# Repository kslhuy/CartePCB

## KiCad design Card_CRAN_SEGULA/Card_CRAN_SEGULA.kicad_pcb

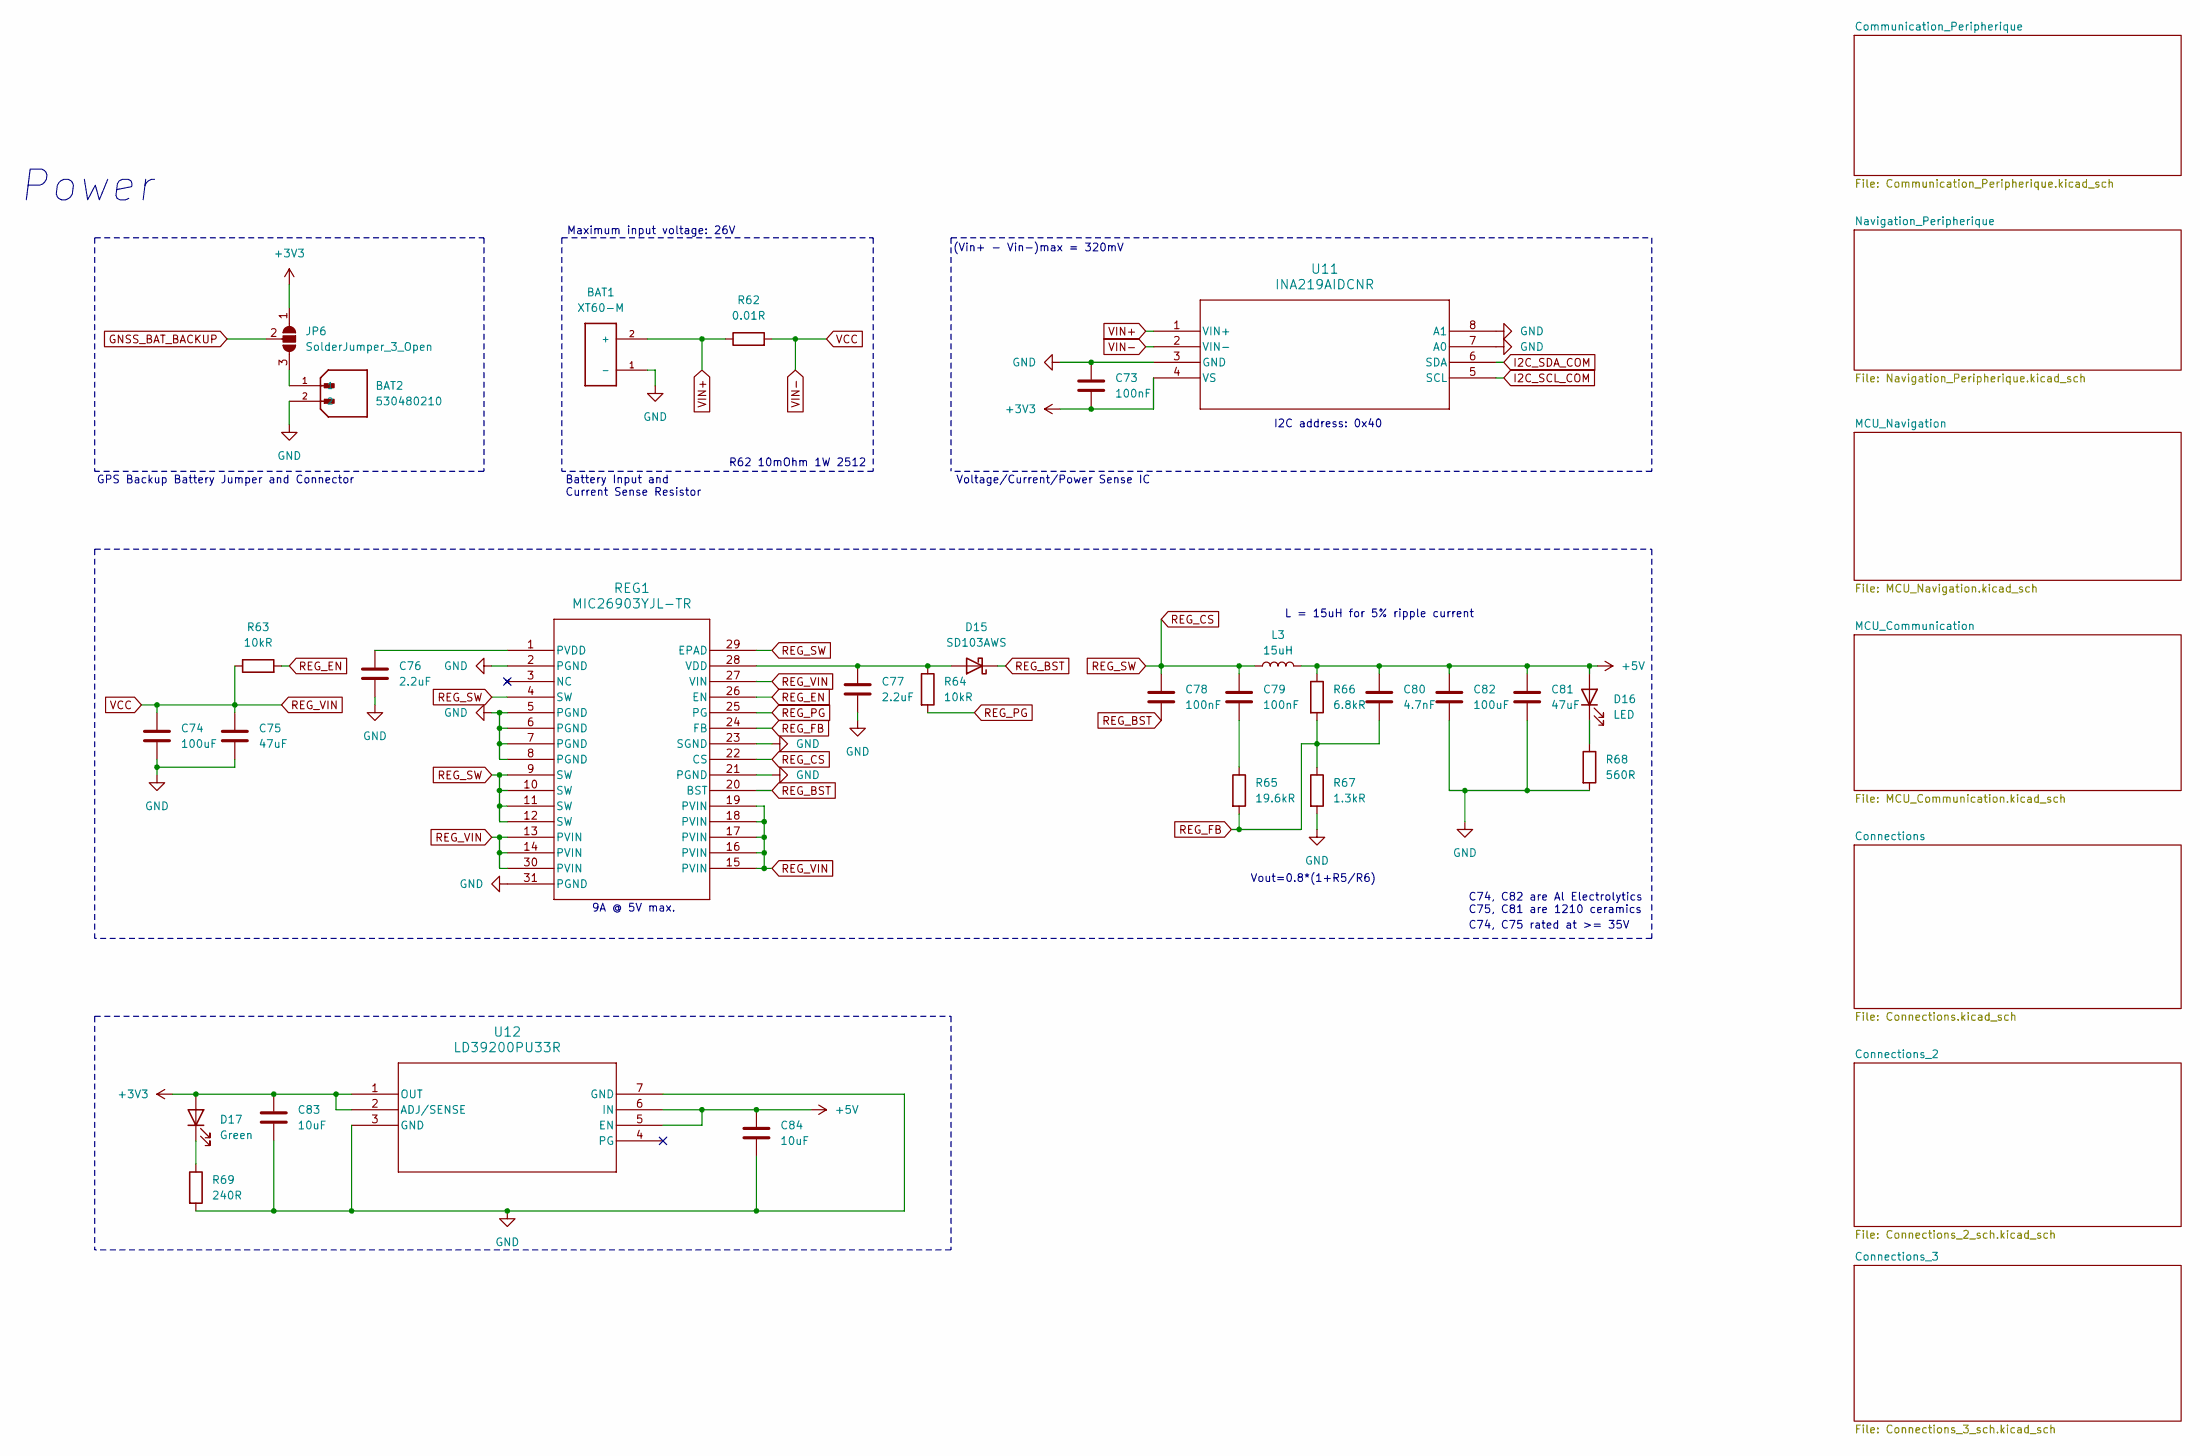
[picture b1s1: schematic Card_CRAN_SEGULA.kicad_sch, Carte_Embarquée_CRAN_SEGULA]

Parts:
BAT1: XT60-M; AMASS_XT60-M
BAT2: 530480210; MOLEX_530480210; PARTREV A
C73: 100nF; CAPC1005X55N
C74, C82: 100uF; CAP_EEEFPV101XAV
C75, C81: 47uF; CAP_C5750X7R1V476M230KC
C76, C77: 2.2uF; CAPC220145_140N_KEM
C78, C79: 100nF; CAPC230155_120N_KEM
C80: 4.7nF; CAPC220145_100N_KEM
C83, C84: 10uF; CAPC1608X100N
D15: SD103AWS; D_SOD-323
D16: LED; 599-0081-007F_DIA
D17: Green; 599-0081-007F_DIA
JP6: SolderJumper_3_Open; SolderJumper-3_P1.3mm_Open_RoundedPad1.0x1.5mm
L3: 15uH; IND_SRP1265A-150M
R62: 0.01R; RES_PE2512_YAG
R63, R64: 10kR; RESC2012X70N
R65: 19.6kR; RES_ERJ-PB6B1962V
R66: 6.8kR; RESC2012X60N
R67: 1.3kR; RK73H2ATTD1301F
R68: 560R; RES_ERJPA3F5600V
R69: 240R; RES_ERJPA3F2400V
REG1: MIC26903YJL-TR; MIC24054YJLTR
U11: INA219AIDCNR; DCN8
U12: LD39200PU33R; SON_DFN6_3X3_STM

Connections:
+5V: C80.1, C81.1, C82.1, C84.1, D16.2 (A), L3.2, R66.1, U12.5 (EN), U12.6 (IN); also elsewhere on the board
GND: BAT1.1 (-), BAT2.2, C73.1, C74.2, C75.2, C76.2, C77.2, C81.2, C82.2, C83.2, C84.2, R67.2, R68.2, R69.2, REG1.2 (PGND), REG1.5 (PGND), REG1.6 (PGND), REG1.7 (PGND), REG1.8 (PGND), REG1.21 (PGND), REG1.23 (SGND), REG1.31 (PGND), U11.3 (GND), U11.7 (A0), U11.8 (A1), U12.3 (GND), U12.7 (GND); also elsewhere on the board
GNSS_BAT_BACKUP: JP6.2 (C); also elsewhere on the board
I2C_SCL_COM: U11.5 (SCL); also elsewhere on the board
I2C_SDA_COM: U11.6 (SDA); also elsewhere on the board
unnamed: C79.2, R65.1
unnamed: C77.1, D15.2 (A), R64.1, REG1.28 (VDD)
unnamed: D16.1 (K), R68.1
unnamed: D17.1 (K), R69.1
unnamed: BAT2.1, JP6.3 (B)
unnamed: C76.1, REG1.1 (PVDD)
REG_BST: C78.2, D15.1 (K), REG1.20 (BST)
REG_CS: C78.1, C79.1, L3.1, REG1.4 (SW), REG1.9 (SW), REG1.10 (SW), REG1.11 (SW), REG1.12 (SW), REG1.22 (CS), REG1.29 (EPAD)
REG_EN: R63.2, REG1.26 (EN)
REG_FB: C80.2, R65.2, R66.2, R67.1, REG1.24 (FB)
REG_PG: R64.2, REG1.25 (PG)
REG_VIN: C74.1, C75.1, R62.2, R63.1, REG1.13 (PVIN), REG1.14 (PVIN), REG1.15 (PVIN), REG1.16 (PVIN), REG1.17 (PVIN), REG1.18 (PVIN), REG1.19 (PVIN), REG1.27 (VIN), REG1.30 (PVIN), U11.2 (VIN-)
VIN+: BAT1.2 (+), R62.1, U11.1 (VIN+)
WIFI_BUCVBATS: C73.2, C83.1, D17.2 (A), JP6.1 (A), U11.4 (VS), U12.1 (OUT), U12.2 (ADJ/SENSE); also elsewhere on the board

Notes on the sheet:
Vout=0.8*(1+R5/R6)
R62 10mOhm 1W 2512
Maximum input voltage: 26V
9A @ 5V max.
Battery Input and Current Sense Resistor
I2C address: 0x40
C74, C82 are Al Electrolytics C75, C81 are 1210 ceramics
L = 15uH for 5% ripple current
Voltage/Current/Power Sense IC
GPS Backup Battery Jumper and Connector
(Vin+ - Vin-)max = 320mV
C74, C75 rated at >= 35V
Power

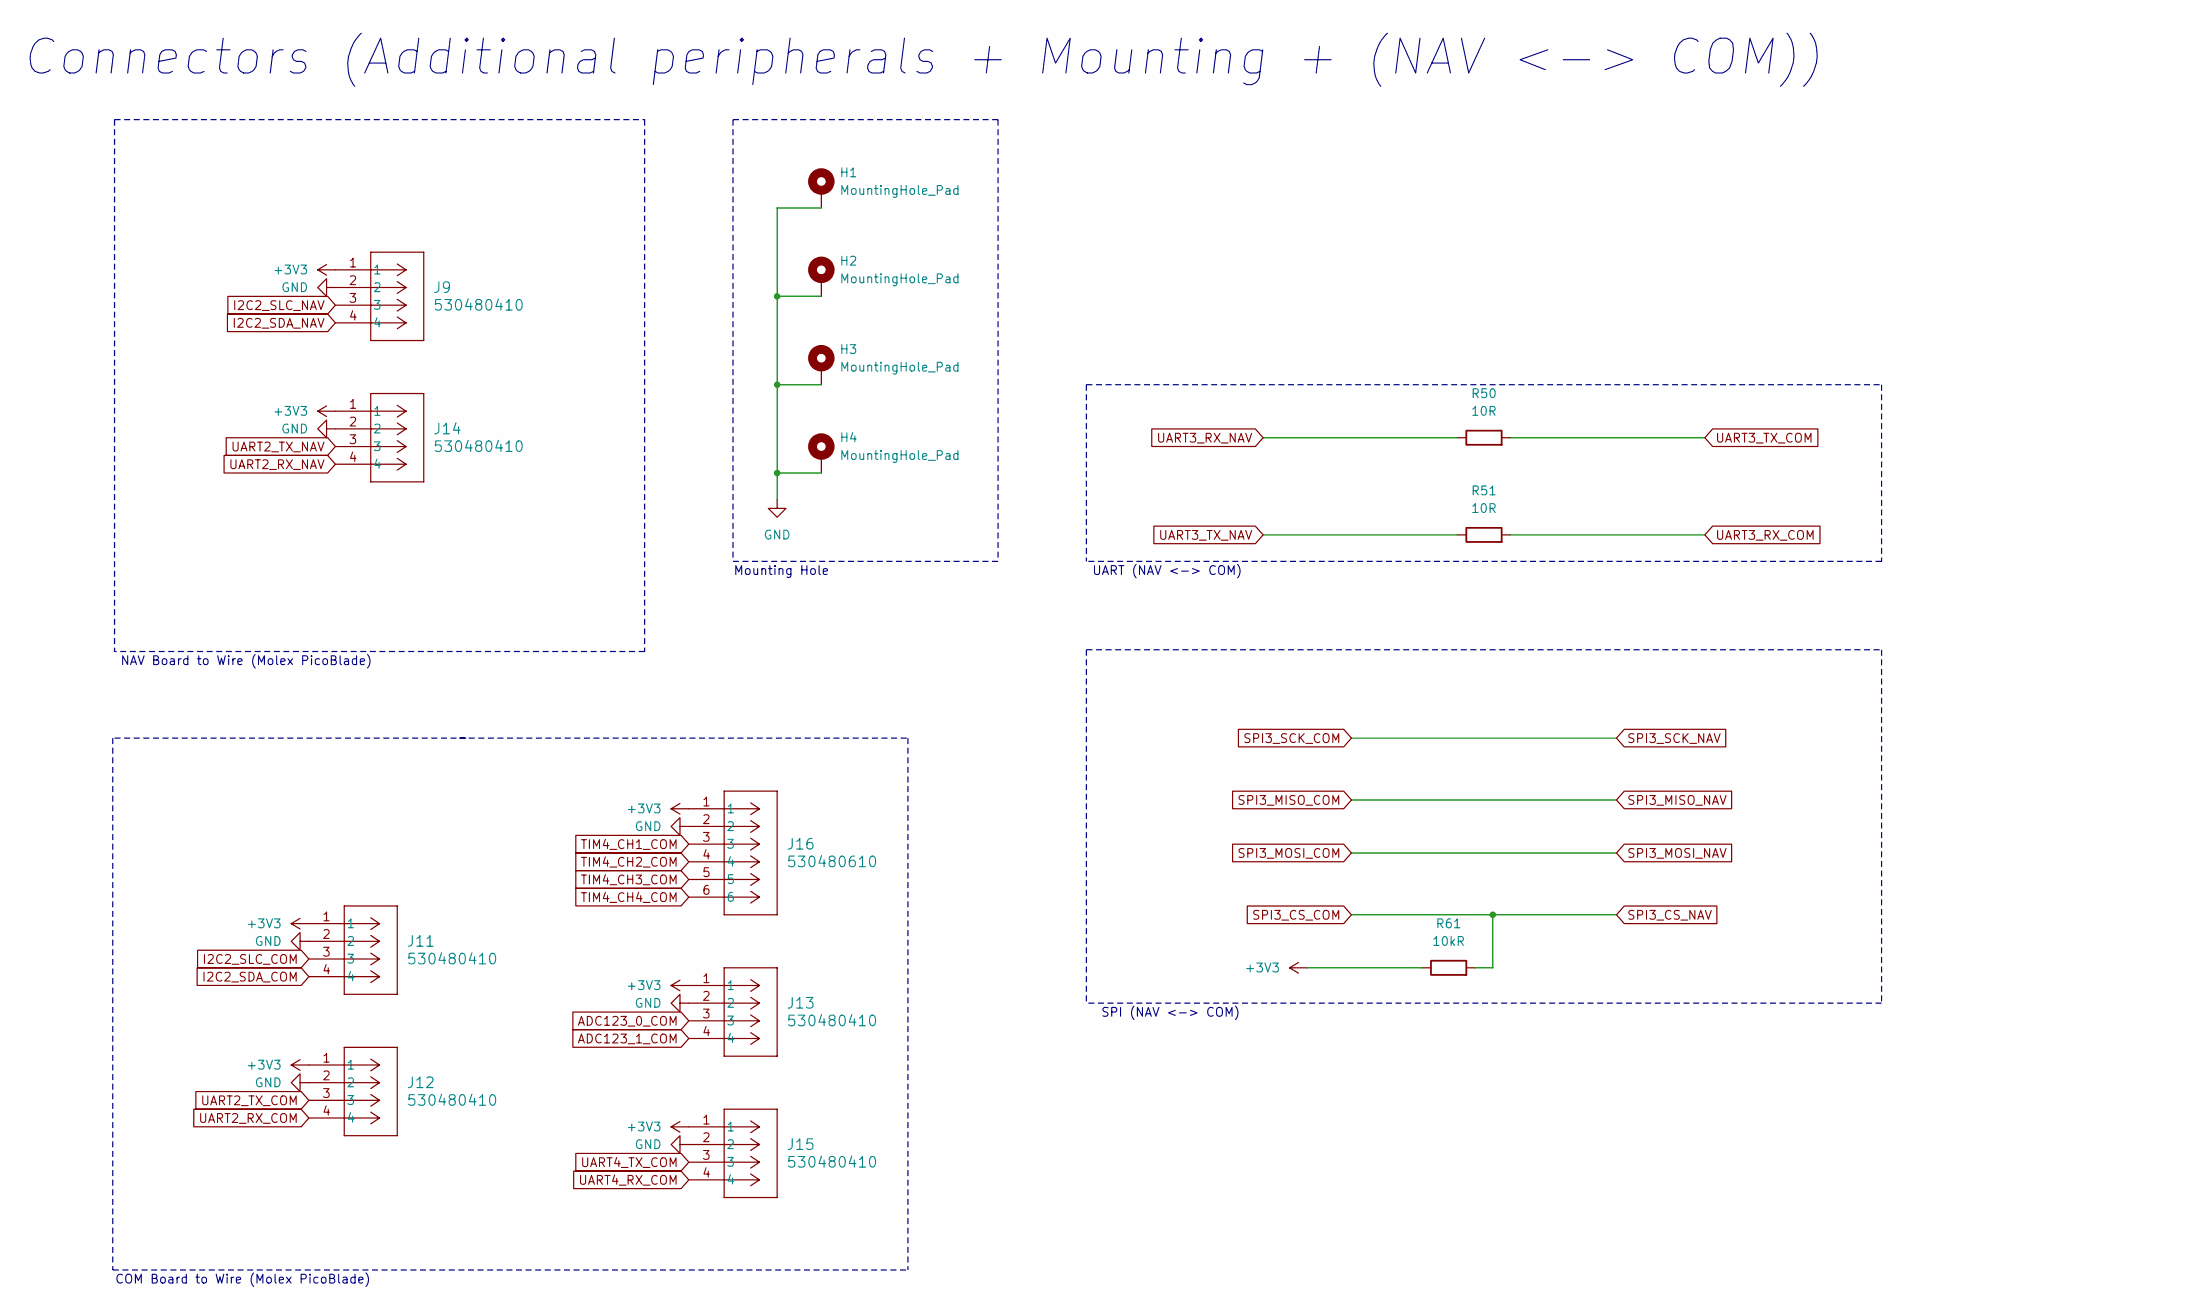
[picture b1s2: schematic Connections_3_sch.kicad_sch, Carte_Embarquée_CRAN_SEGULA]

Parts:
H1, H2, H3, H4: MountingHole_Pad; MountingHole_3.2mm_M3_Pad_Via
J9, J11, J12, J13, J14, J15: 530480410; CONN04_530480410_MOL
J16: 530480610; CONN06_530480610_MOL
R50, R51: 10R; RES_ERA2AKD100X
R61: 10kR; RESC1105X40N

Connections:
ADC123_0_COM: J13.3; also elsewhere on the board
ADC123_1_COM: J13.4; also elsewhere on the board
GND: H1.1, H2.1, H3.1, H4.1, J9.2, J11.2, J12.2, J13.2, J14.2, J15.2, J16.2; also elsewhere on the board
I2C2_SDA_COM: J11.4; also elsewhere on the board
I2C2_SDA_NAV: J9.4; also elsewhere on the board
I2C2_SLC_COM: J11.3; also elsewhere on the board
I2C2_SLC_NAV: J9.3; also elsewhere on the board
SPI3_CS_COM: R61.2; also elsewhere on the board
TIM4_CH1_COM: J16.3; also elsewhere on the board
TIM4_CH2_COM: J16.4; also elsewhere on the board
TIM4_CH3_COM: J16.5; also elsewhere on the board
TIM4_CH4_COM: J16.6; also elsewhere on the board
UART2_RX_COM: J12.4; also elsewhere on the board
UART2_RX_NAV: J14.4; also elsewhere on the board
UART2_TX_COM: J12.3; also elsewhere on the board
UART2_TX_NAV: J14.3; also elsewhere on the board
UART3_RX_COM: R51.2; also elsewhere on the board
UART3_RX_NAV: R50.1; also elsewhere on the board
UART3_TX_COM: R50.2; also elsewhere on the board
UART3_TX_NAV: R51.1; also elsewhere on the board
UART4_RX_COM: J15.4; also elsewhere on the board
UART4_TX_COM: J15.3; also elsewhere on the board
WIFI_BUCVBATS: J9.1, J11.1, J12.1, J13.1, J14.1, J15.1, J16.1, R61.1; also elsewhere on the board

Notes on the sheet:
NAV Board to Wire (Molex PicoBlade)
SPI (NAV <-> COM)
UART (NAV <-> COM)
COM Board to Wire (Molex PicoBlade)
Connectors (Additional peripherals + Mounting + (NAV <-> COM))
Mounting Hole

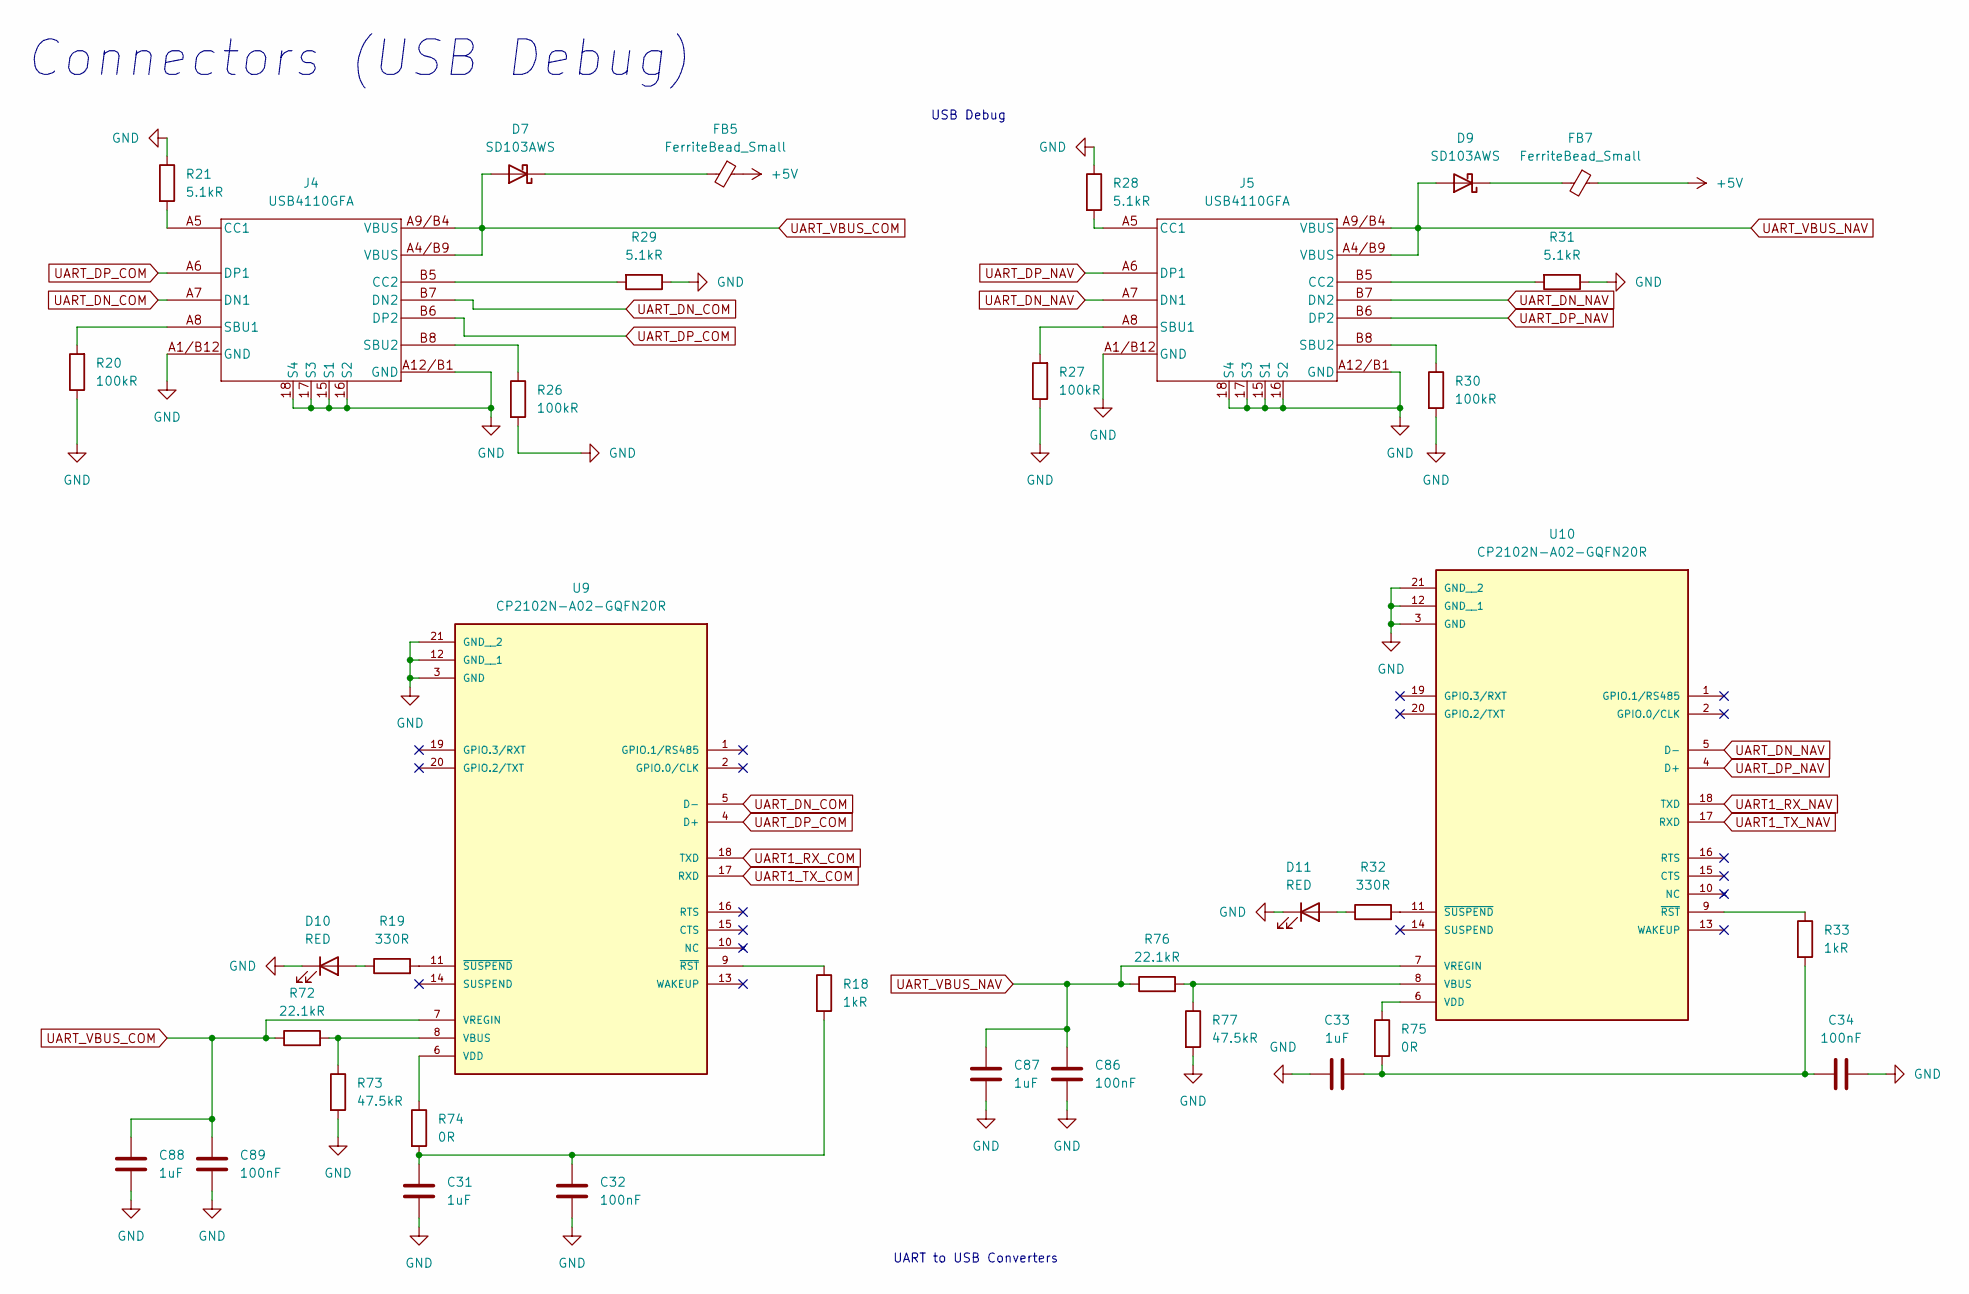
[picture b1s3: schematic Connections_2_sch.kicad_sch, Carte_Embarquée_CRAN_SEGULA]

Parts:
C31, C33, C87, C88: 1uF; CAPC17595_90N_KEM
C32, C34, C86, C89: 100nF; CAPC1005X55N
D7, D9: SD103AWS; D_SOD-323
D10, D11: RED; 599-0001-007F_DIA
FB5, FB7: FerriteBead_Small; L_0402_1005Metric
J4, J5: USB4110GFA; USB4110-GF-A_GCT
R18, R33: 1kR; RESC1005X40N
R19, R32: 330R; RES_ERJPA3D3300V
R20, R26, R27, R30: 100kR; RES_ERJ2RKF1003X
R21, R28, R29, R31: 5.1kR; RES_ERJ2RKF5101X
R72, R76: 22.1kR; RESC1005X40N
R73, R77: 47.5kR; RESC1005X40N
R74, R75: 0R; RESC1508X50N
U9, U10: CP2102N-A02-GQFN20R; QFN20_SIL; PARTREV 1.3

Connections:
+5V: FB5.1, FB7.1; also elsewhere on the board
GND: C31.2, C32.2, C33.2, C34.2, C86.2, C87.2, C88.2, C89.2, D10.1 (K), D11.1 (K), J4.15 (S1), J4.16 (S2), J4.17 (S3), J4.18 (S4), J4.A1/B12 (GND), J4.A12/B1 (GND), J5.15 (S1), J5.16 (S2), J5.17 (S3), J5.18 (S4), J5.A1/B12 (GND), J5.A12/B1 (GND), R20.1, R21.1, R26.2, R27.1, R28.1, R29.1, R30.2, R31.1, R73.2, R77.2, U9.3 (GND), U9.12 (GND__1), U9.21 (GND__2), U10.3 (GND), U10.12 (GND__1), U10.21 (GND__2); also elsewhere on the board
unnamed: C31.1, C32.1, R18.2, R74.2
unnamed: C33.1, C34.1, R33.2, R75.2
unnamed: D7.1 (K), FB5.2
unnamed: D9.1 (K), FB7.2
unnamed: D10.2 (A), R19.1
unnamed: D11.2 (A), R32.1
unnamed: J4.A5 (CC1), R21.2
unnamed: J4.B5 (CC2), R29.2
unnamed: J4.A8 (SBU1), R20.2
unnamed: J4.B8 (SBU2), R26.1
unnamed: J5.A5 (CC1), R28.2
unnamed: J5.B5 (CC2), R31.2
unnamed: J5.A8 (SBU1), R27.2
unnamed: J5.B8 (SBU2), R30.1
unnamed: R72.2, R73.1, U9.8 (VBUS)
unnamed: R74.1, U9.6 (VDD)
unnamed: R18.1, U9.9 (~RST)
unnamed: R19.2, U9.11 (~SUSPEND)
unnamed: R76.2, R77.1, U10.8 (VBUS)
unnamed: R75.1, U10.6 (VDD)
unnamed: R33.1, U10.9 (~RST)
unnamed: R32.2, U10.11 (~SUSPEND)
UART1_RX_COM: U9.18 (TXD); also elsewhere on the board
UART1_RX_NAV: U10.18 (TXD); also elsewhere on the board
UART1_TX_COM: U9.17 (RXD); also elsewhere on the board
UART1_TX_NAV: U10.17 (RXD); also elsewhere on the board
UART_DN_COM: J4.A7 (DN1), J4.B7 (DN2), U9.5 (D-)
UART_DN_NAV: J5.A7 (DN1), J5.B7 (DN2), U10.5 (D-)
UART_DP_COM: J4.A6 (DP1), J4.B6 (DP2), U9.4 (D+)
UART_DP_NAV: J5.A6 (DP1), J5.B6 (DP2), U10.4 (D+)
UART_VBUS_COM: C88.1, C89.1, D7.2 (A), J4.A4/B9 (VBUS), J4.A9/B4 (VBUS), R72.1, U9.7 (VREGIN)
UART_VBUS_NAV: C86.1, C87.1, D9.2 (A), J5.A4/B9 (VBUS), J5.A9/B4 (VBUS), R76.1, U10.7 (VREGIN)

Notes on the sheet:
UART to USB Converters
USB Debug
Connectors (USB Debug)

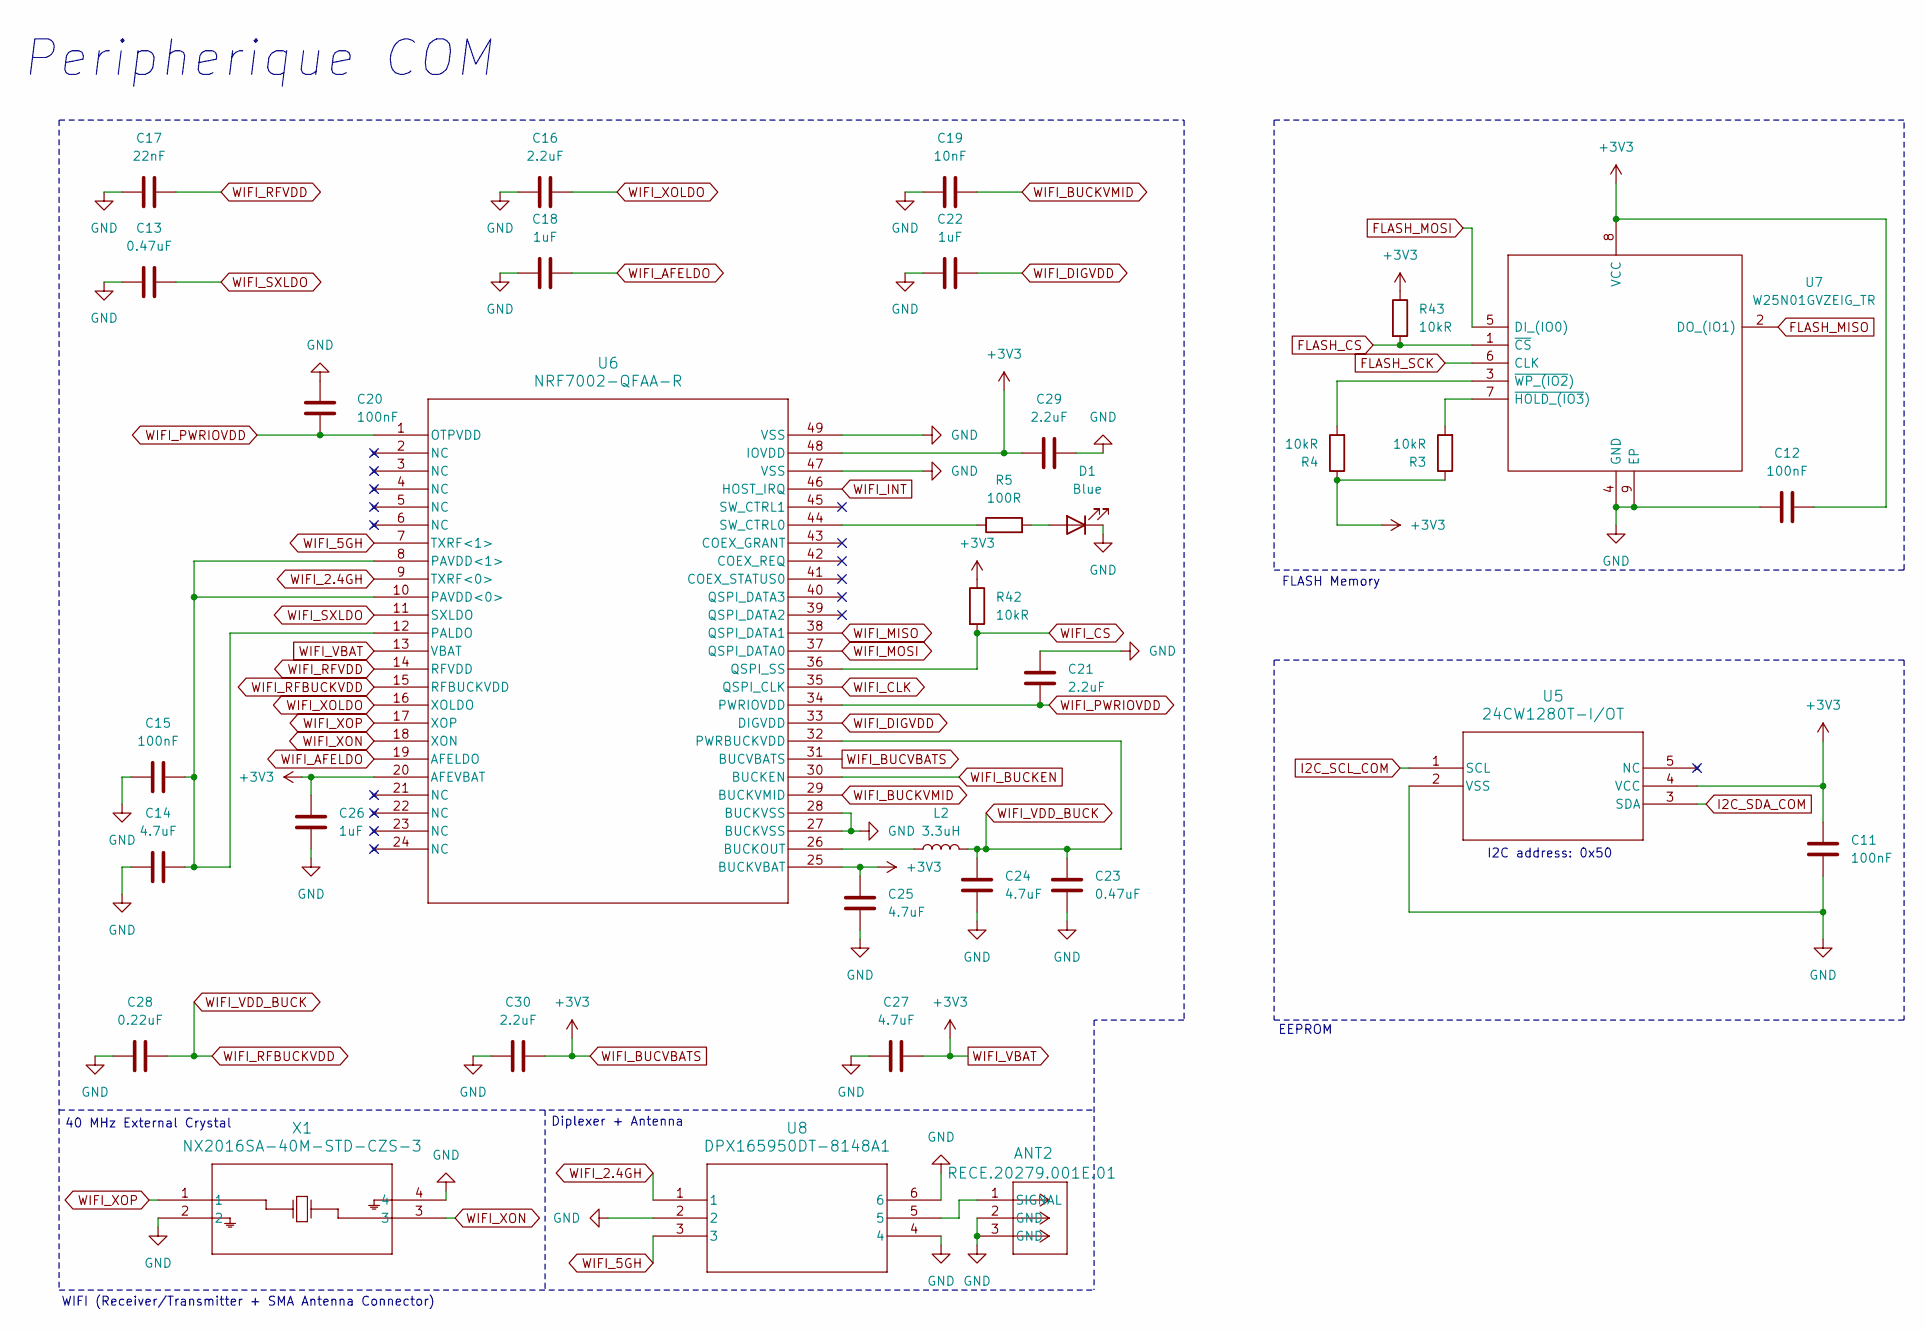
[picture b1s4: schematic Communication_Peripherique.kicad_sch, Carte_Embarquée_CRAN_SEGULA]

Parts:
ANT2: RECE.20279.001E.01; CON3_RECE.20279.001E.01_TAL
C11, C12: 100nF; CAPC1005X55N
C13, C23: 0.47uF; CAPC0603X33N
C14, C24, C25, C27: 4.7uF; CAPC1608X100N
C15, C20: 100nF; CAPC0603X33N
C16, C29, C30: 2.2uF; CAPC1608X100N
C17: 22nF; CAPC0603X33N
C18: 1uF; CAPC1005X70N
C19: 10nF; CAPC1005X55N
C21: 2.2uF; CAPC1005X70N
C22, C26: 1uF; CAPC1005X60N
C28: 0.22uF; CAPC0603X33N
D1: Blue; 599-0091-007F_DIA
L2: 3.3uH; WE-PMI_0805_H1
R3, R4, R42, R43: 10kR; RESC1105X40N
R5: 100R; RES_ERJPA3D1000V
U5: 24CW1280T-I/OT; SOT-23-5_2P9X1P6_MCH
U6: NRF7002-QFAA-R; QFN48_6X6_NOR
U7: W25N01GVZEIG_TR; SON127P800X600X80-9N-D; Manufacturer_Part_Number W25N01GVZEIG TR; Mouser Part Number 454-W25N01GVZEIGTR
U8: DPX165950DT-8148A1; RF_5049A1_TDK
X1: NX2016SA-40M-STD-CZS-3; NX2016SA-40M-STD-CZS-3_NDK

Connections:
FLASH_CS: R43.2, U7.1 (~CS); also elsewhere on the board
FLASH_MISO: U7.2 (DO_(IO1)); also elsewhere on the board
FLASH_MOSI: U7.5 (DI_(IO0)); also elsewhere on the board
FLASH_SCK: U7.6 (CLK); also elsewhere on the board
GND: ANT2.2 (GND), ANT2.3 (GND), C11.2, C12.1, C13.1, C14.2, C15.1, C16.1, C17.2, C18.1, C19.1, C20.1, C21.1, C22.1, C23.2, C24.2, C25.2, C26.1, C27.1, C28.1, C29.2, C30.1, D1.1 (K), U5.2 (VSS), U6.27 (BUCKVSS), U6.28 (BUCKVSS), U6.47 (VSS), U6.49 (VSS), U7.4 (GND), U7.9 (EP), U8.2, U8.4, U8.6, X1.2, X1.4; also elsewhere on the board
I2C_SCL_COM: U5.1 (SCL); also elsewhere on the board
I2C_SDA_COM: U5.3 (SDA); also elsewhere on the board
unnamed: ANT2.1 (SIGNAL), U8.5
unnamed: D1.2 (A), R5.2
unnamed: L2.1, U6.26 (BUCKOUT)
unnamed: C14.1, C15.2, U6.8 (PAVDD<1>), U6.10 (PAVDD<0>), U6.12 (PALDO)
unnamed: R5.1, U6.44 (SW_CTRL0)
unnamed: R3.2, U7.7 (~HOLD_(IO3))
unnamed: R4.2, U7.3 (~WP_(IO2))
WIFI_2.4GH: U6.9 (TXRF<0>), U8.1
WIFI_5GH: U6.7 (TXRF<1>), U8.3
WIFI_AFELDO: C18.2, U6.19 (AFELDO)
WIFI_BUCKEN: U6.30 (BUCKEN); also elsewhere on the board
WIFI_BUCKVMID: C19.2, U6.29 (BUCKVMID)
WIFI_BUCVBATS: C11.1, C12.2, C25.1, C26.2, C27.2, C29.1, C30.2, R3.1, R4.1, R42.1, R43.1, U5.4 (VCC), U6.13 (VBAT), U6.20 (AFEVBAT), U6.25 (BUCKVBAT), U6.31 (BUCVBATS), U6.48 (IOVDD), U7.8 (VCC); also elsewhere on the board
WIFI_CLK: U6.35 (QSPI_CLK); also elsewhere on the board
WIFI_CS: R42.2, U6.36 (QSPI_SS); also elsewhere on the board
WIFI_DIGVDD: C22.2, U6.33 (DIGVDD)
WIFI_INT: U6.46 (HOST_IRQ); also elsewhere on the board
WIFI_MISO: U6.38 (QSPI_DATA1); also elsewhere on the board
WIFI_MOSI: U6.37 (QSPI_DATA0); also elsewhere on the board
WIFI_PWRIOVDD: C20.2, C21.2, U6.1 (OTPVDD), U6.34 (PWRIOVDD)
WIFI_RFBUCKVDD: C23.1, C24.1, C28.2, L2.2, U6.15 (RFBUCKVDD), U6.32 (PWRBUCKVDD)
WIFI_RFVDD: C17.1, U6.14 (RFVDD)
WIFI_SXLDO: C13.2, U6.11 (SXLDO)
WIFI_XOLDO: C16.2, U6.16 (XOLDO)
WIFI_XON: U6.18 (XON), X1.3
WIFI_XOP: U6.17 (XOP), X1.1

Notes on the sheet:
40 MHz External Crystal
I2C address: 0x50
Diplexer + Antenna
Peripherique COM
FLASH Memory
WIFI (Receiver/Transmitter + SMA Antenna Connector)
EEPROM

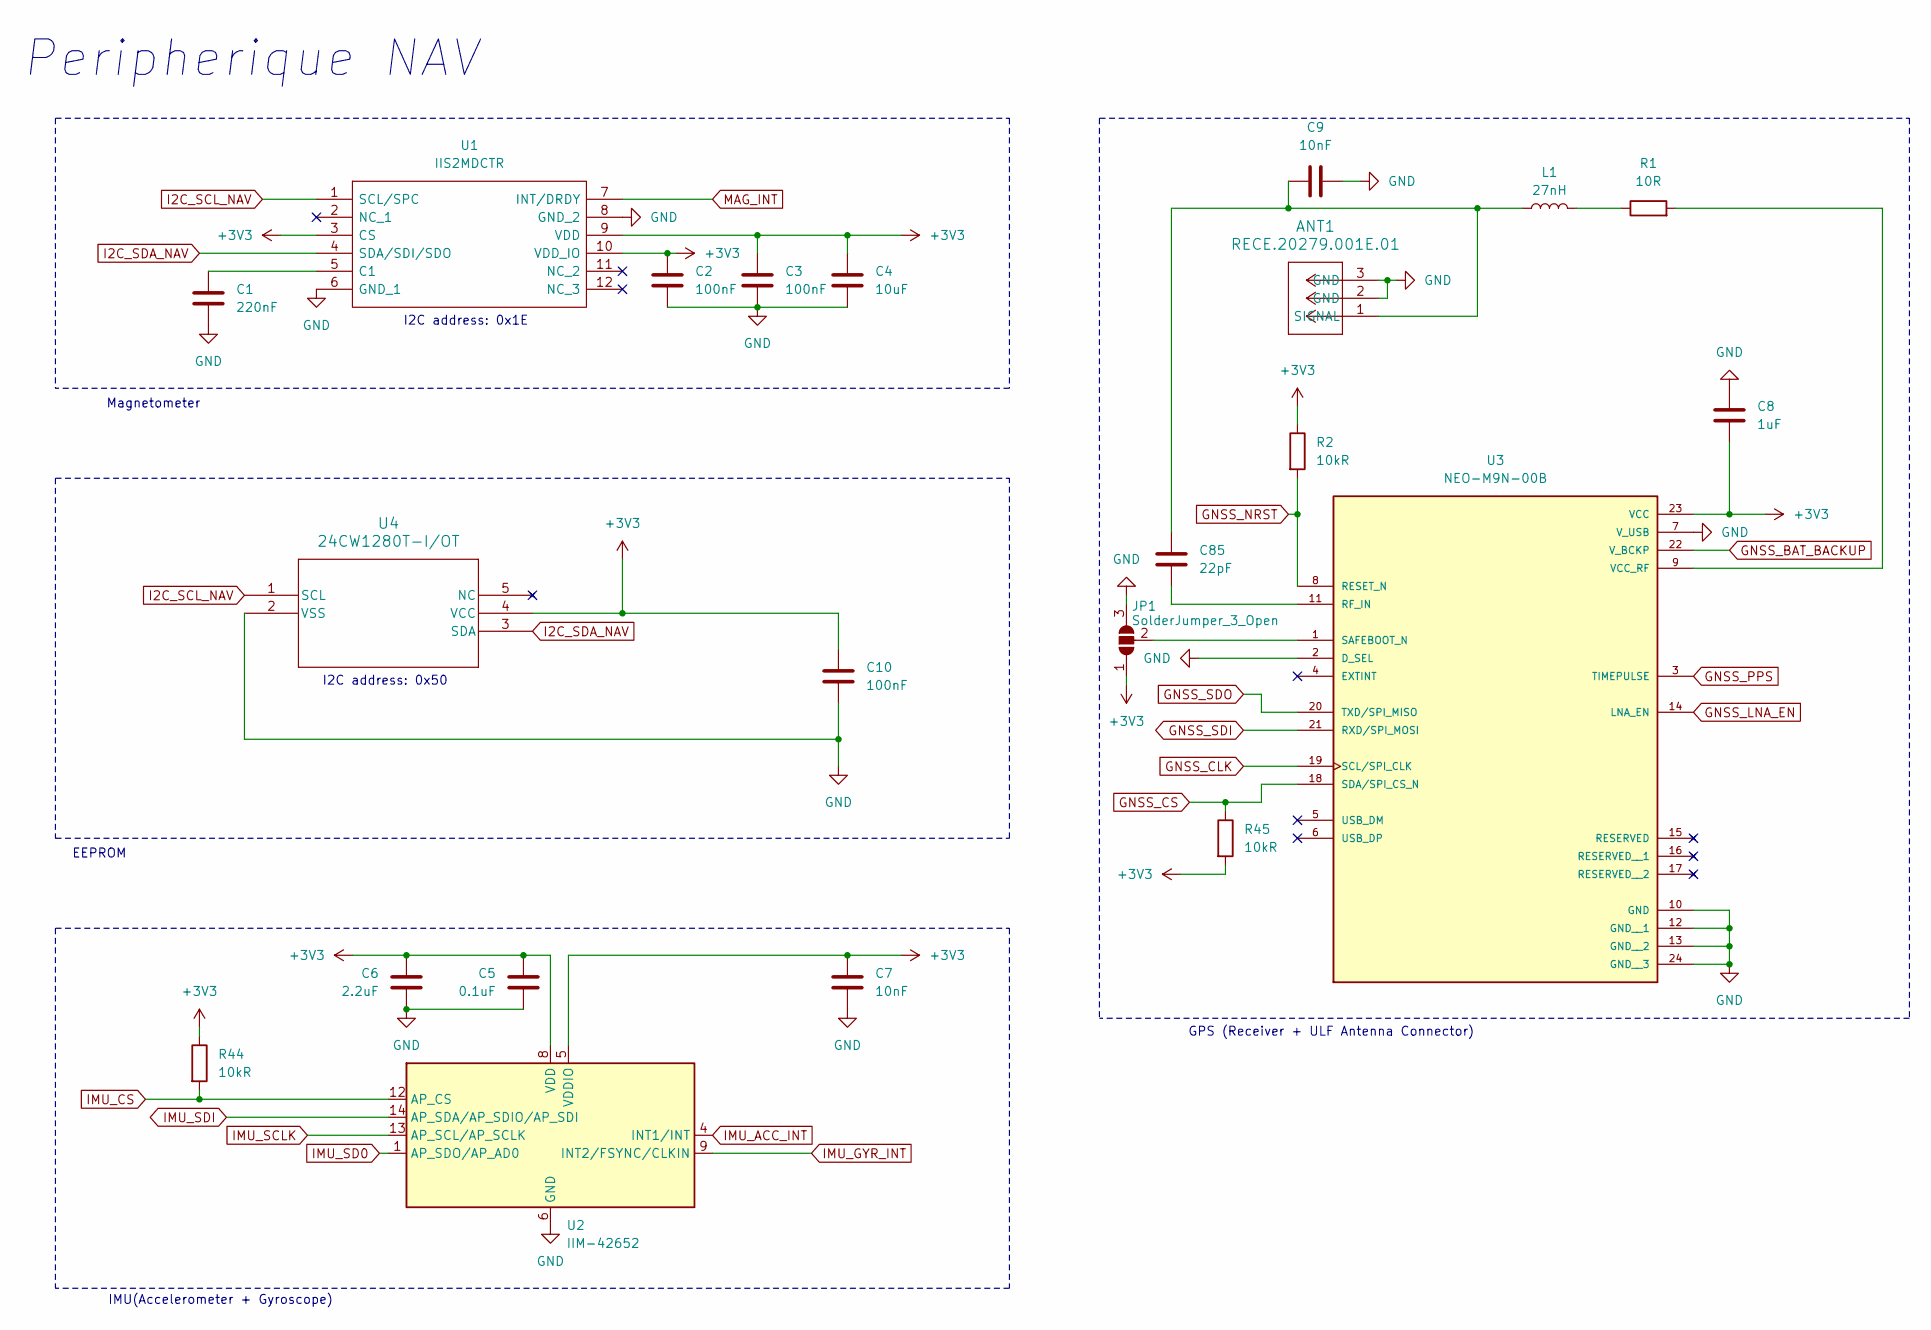
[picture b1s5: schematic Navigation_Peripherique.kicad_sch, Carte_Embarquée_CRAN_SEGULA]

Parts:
ANT1: RECE.20279.001E.01; CON3_RECE.20279.001E.01_TAL
C1: 220nF; CAPC17595_87N_KEM
C2, C3, C10: 100nF; CAPC1005X55N
C4: 10uF; CAPC1608X100N
C5: 0.1uF; CAPC1005X55N
C6: 2.2uF; CAPC1608X100N
C7, C9: 10nF; CAPC1005X55N
C8: 1uF; CAPC17595_90N_KEM
C85: 22pF; CAPC1005X55N
JP1: SolderJumper_3_Open; SolderJumper-3_P1.3mm_Open_RoundedPad1.0x1.5mm
L1: 27nH; INDC1006X60N
R1: 10R; RES_ERA2AKD100X
R2, R44, R45: 10kR; RESC1105X40N
U1: IIS2MDCTR; Manufacturer_Part_Number IIS2MDCTR; Mouser Part Number 511-IIS2MDCTR
U2: IIM-42652; Bosch_LGA-14_3x2.5mm_P0.5mm
U3: NEO-M9N-00B; XCVR_NEO-M9N-00B; PARTREV R05
U4: 24CW1280T-I/OT; SOT-23-5_2P9X1P6_MCH

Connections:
GND: ANT1.2 (GND), ANT1.3 (GND), C1.2, C2.2, C3.2, C4.2, C5.2, C6.2, C7.2, C8.1, C9.1, C10.2, JP1.3 (B), U1.6 (GND_1), U1.8 (GND_2), U2.6 (GND), U2.7 (GND), U3.2 (D_SEL), U3.7 (V_USB), U3.10 (GND), U3.12 (GND__1), U3.13 (GND__2), U3.24 (GND__3), U4.2 (VSS); also elsewhere on the board
GNSS_BAT_BACKUP: U3.22 (V_BCKP); also elsewhere on the board
GNSS_CLK: U3.19 (SCL/SPI_CLK); also elsewhere on the board
GNSS_CS: R45.1, U3.18 (SDA/SPI_CS_N); also elsewhere on the board
GNSS_LNA_EN: U3.14 (LNA_EN); also elsewhere on the board
GNSS_NRST: R2.2, U3.8 (RESET_N); also elsewhere on the board
GNSS_PPS: U3.3 (TIMEPULSE); also elsewhere on the board
GNSS_SDI: U3.21 (RXD/SPI_MOSI); also elsewhere on the board
GNSS_SDO: U3.20 (TXD/SPI_MISO); also elsewhere on the board
I2C_SCL_NAV: U1.1 (SCL/SPC), U4.1 (SCL); also elsewhere on the board
I2C_SDA_NAV: U1.4 (SDA/SDI/SDO), U4.3 (SDA); also elsewhere on the board
IMU_ACC_INT: U2.4 (INT1/INT); also elsewhere on the board
IMU_CS: R44.2, U2.12 (AP_CS); also elsewhere on the board
IMU_GYR_INT: U2.9 (INT2/FSYNC/CLKIN); also elsewhere on the board
IMU_SCLK: U2.13 (AP_SCL/AP_SCLK); also elsewhere on the board
IMU_SD0: U2.1 (AP_SDO/AP_AD0); also elsewhere on the board
IMU_SDI: U2.14 (AP_SDA/AP_SDIO/AP_SDI); also elsewhere on the board
MAG_INT: U1.7 (INT/DRDY); also elsewhere on the board
unnamed: ANT1.1 (SIGNAL), C9.2, C85.1, L1.1
unnamed: JP1.2 (C), U3.1 (SAFEBOOT_N)
unnamed: L1.2, R1.1
unnamed: C1.1, U1.5 (C1)
unnamed: C85.2, U3.11 (RF_IN)
unnamed: R1.2, U3.9 (VCC_RF)
WIFI_BUCVBATS: C2.1, C3.1, C4.1, C5.1, C6.1, C7.1, C8.2, C10.1, JP1.1 (A), R2.1, R44.1, R45.2, U1.3 (CS), U1.9 (VDD), U1.10 (VDD_IO), U2.5 (VDDIO), U2.8 (VDD), U3.23 (VCC), U4.4 (VCC); also elsewhere on the board

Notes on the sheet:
Peripherique NAV
I2C address: 0x1E
I2C address: 0x50
Magnetometer
IMU(Accelerometer + Gyroscope)
GPS (Receiver + ULF Antenna Connector)
EEPROM
